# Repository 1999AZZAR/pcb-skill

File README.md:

# PCB Agent Skill

Autonomous, end-to-end PCB design, schematic capture, layout, routing, verification, and manufacturing exporter for AI coding agents (**Antigravity**, **Claude Code**, **Codex**).

Drives **KiCad 9** natively via headless command-line interfaces (`kicad-cli`), Python bindings (`pcbnew`), and direct S-expression manipulation.

---

## 1. Core Principles

1. **性价比 (Cost-Effectiveness)**: Every component is matched against real-world LCSC/JLCPCB catalog availability and pricing, netted against inventory on hand.
2. **好装配 (Hand & SMT Assemblable)**: Geometrically verified pad reachability, component orientation validation, and collision-free clearance zones.
3. **零缺陷 (Zero-Error Manufacturing Yield)**: Strict gates requiring **0 DRC errors, 0 warnings, and 0 unconnected nets** before exporting fabrication-ready packages.

---

## 2. Key Features & Architecture

* **Unified KiCad Automation Controller ([`kicad_ctl.py`](scripts/kicad/kicad_ctl.py))**:
  * 233 programmatic automation commands spanning schematics, footprints, routing, placement, netlists, and DRC checks.
  * Headless execution without requiring GUI interaction or display servers.

* **Connector Edge Orientation Engine ([`connector_rules.py`](scripts/kicad/core/connector_rules.py))**:
  * Eliminates backwards / reversed connector placement bugs.
  * Resolves KiCad library coordinate disparities where default 0° mating faces vary (USB Type-C points South $+Y$, 3.5mm Audio Jacks point West $-X$).
  * Enforces exact outward edge rotation angles across any board edge ($W=270^\circ$, $E=90^\circ$ for USB-C; $E=180^\circ$, $W=0^\circ$ for Audio Jacks).

* **Pre-Flight Placement & Clearance Validator ([`placement_validator.py`](scripts/kicad/core/placement_validator.py))**:
  * Replaces slow, iterative DRC trial-and-error with $<100\,\text{ms}$ mathematical pre-flight validation.
  * Audits true IPC courtyard polygon collisions (`F.CrtYd` / `B.CrtYd`), connector edge alignments, and $\ge 0.5\,\text{mm}$ board-edge clearances.
  * Seamlessly integrated into `scripts/kicad/drc_check.py` and `kicad_ctl.py audit-placement`.

* **Deterministic 2-Layer Router ([`autoroute_2layer.py`](scripts/kicad/autoroute_2layer.py))**:
  * Programmatic 2-layer layout builder enforcing the **5 Golden Rules**:
    1. Solid unbroken bottom ground plane (`B.Cu`).
    2. Dedicated local SMD GND via stubs straight to ground plane.
    3. Decoupled orthogonal routing (Top horizontal, Bottom short vertical jumpers).
    4. Outer margin power distribution trunks.
    5. Pin header column segregation (no diagonal crossing).
  * Built-in keepout rule area generator with explicit KiCad 9 permission flag handling.
  * Pad-level thermal relief spoke control (`ZONE_CONNECTION_FULL`) to prevent `starved_thermal` violations.

* **Hardened KiCad 9 Headless Engine**:
  * **Rule Area Permission Safety**: Prevents default blocking of tracks/vias when adding copper-pour keepouts.
  * **SWIG Iterator Guarding**: Protects against C++ pointer invalidation crashes during track deletion.
  * **Zone Island Topology Diagnostics**: Programmatic contour scanning via `zone.GetFilledPolysList()` to locate and bridge isolated ground flood islands.
  * **Rotated Pad Geometry Clearances**: Anisotropic clearance evaluations accounting for $90^\circ / 270^\circ$ orientation swaps.

* **1-Command JLCPCB Fabrication Exporter ([`export_jlcpcb.py`](scripts/kicad/export_jlcpcb.py))**:
  * RS-274X Gerbers (no X2, subtract soldermask, drill origin, 6-decimal precision).
  * Excellon drill files (separate PTH/NPTH, metric decimal).
  * JLCPCB-formatted CPL / Pick-and-Place centroid file.
  * LCSC catalog-matched Bill of Materials (BOM).
  * Photorealistic top and bottom 3D raytraced preview renders.
  * Production ZIP archive ready for 1-click ordering.
  * Independent drill census and board outline verification checkers.

---

## 3. Four-Phase Workflow Pipeline

| Phase | Output Deliverables | Gate Requirement |
| :--- | :--- | :--- |
| **1. Concept** | Functional specifications, pinout table, mechanical constraints | User confirms all physical and electrical trade-offs |
| **2. Schematic & Sourcing** | Validated `.kicad_sch`, embedded library symbols, priced BOM | `kicad-cli sch erc` passes clean; all nets asserted |
| **3. Layout & Routing** | Placed, routed, and poured `.kicad_pcb` | `kicad-cli pcb drc` **0 errors / 0 unconnected items** |
| **4. Fabrication** | Gerber archive, CPL, BOM, 3D renders in `jlcpcb_production/` | Independent verification scripts pass; package census clean |

---

## 4. Repository Structure

```
pcb-skill/
├── scripts/
│   ├── kicad/               # KiCad controller, 2-layer router, cleanup engine, JLCPCB exporter
│   ├── placement/           # Footprint courtyards, keepout checkers, clearance analysis
│   ├── routing/             # DSN/SES router runners, watchdog monitors
│   ├── verify/              # Netlist assertions, Gerber parser, drill census
│   └── run_all_tests.py     # 20-check automated regression test suite
├── skills/
│   └── pcb/
│       ├── SKILL.md         # Agent skill manifest & instruction prompt
│       └── references/      # Workflow rules, review protocols, JLC limits, bringup guides
├── docs/                    # Architecture documentation & case studies
├── setup/                   # Setup guides for KiCad, headless CLI, and browser integration
└── README.md
```

---

## 5. Automated Verification

Run the full headless test suite:

```bash
python3 scripts/run_all_tests.py
```

Validates toolchain availability, command dispatchers, board cleanup, router SES integration, DRC parsing, schematic symbol embedding, and live THT / SMT project rule checks.

---

## 6. Acknowledgments & Lineage

This skill builds upon, extends, and synthesizes concepts from two foundational open-source projects:

1. **[`daishuge/pcb-skill`](https://github.com/daishuge/pcb-skill)**:
   * Originator of the agentic hardware design workflow, real-world gating protocols, adversarial review methodology, and sourcing automation principles.
2. **[`mixelpixx/KiCAD-MCP-Server`](https://github.com/mixelpixx/KiCAD-MCP-Server)**:
   * Pioneer in programmatic KiCad automation, headless command dispatch architecture, and Model Context Protocol (MCP) tooling for computer-aided PCB design.

---

## 7. License

MIT License. See [LICENSE](LICENSE) for details.

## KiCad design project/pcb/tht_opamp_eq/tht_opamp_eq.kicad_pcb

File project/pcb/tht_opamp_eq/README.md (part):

# THT 3.3V Stereo 3-Band Equalizer & Preamp

An ultra-compact, high-fidelity, 100% Through-Hole (THT) stereo audio equalizer and headphone/line preamplifier designed for 3.3V battery or single-supply operation.

Zero surface-mount components. Optimized for hand soldering, DIY audio gear, portable headphone setups, and custom instrument tone shaping.

---

## Highlights & Specifications

| Parameter | Specification | Details |
|---|---|---|
| **Form Factor** | 88.0 mm × 61.0 mm | Ultra-compact 2-layer PCB |
| **Component Technology** | 100% Through-Hole (THT) | Easy hand assembly with basic iron |
| **Supply Voltage** | 3.3V DC (1.8V to 5.5V tolerated) | Single-cell LiFePO4, 3.7V Li-Ion (via LDO), or 2x/3x AA |
| **Active Core** | Microchip MCP6004 (DIP-14) | Quad Rail-to-Rail I/O CMOS Op-Amp |
| **Quiescent Current** | ~3.0 mA total (including LED) | Extremely power-efficient for battery use |
| **Input / Output** | Dual 3.5 mm TRS Stereo Jacks | AC-coupled audio line & headphone drive |
| **Tone Controls** | Bass, Mid, Treble (±10 to 12 dB) | Active feedback Baxandall topology |
| **Volume & Balance** | Log Volume + Linear Balance | Independent stereo level and stereo imaging |
| **Grounding** | Solid `B.Cu` Ground Plane | Full ground pour for minimum hum and noise |
| **Mounting** | 4× M3 Mounting Holes | 4.0 mm inset from board corners |
| **DRC Compliance** | **0 Errors, 0 Warnings, 0 Unconnected Nets** | 100% clean KiCad strict DRC pass |

---

## Circuit Architecture

```text
[3.5mm Stereo IN] 
       │
       ▼ (1 µF AC Coupling)
[VOL Potentiometer (50k Log)] 
       │
       ▼
[Active 3-Band Baxandall Filter] ── MCP6004 (U1A / U1D)
  ├── BASS  (100k Linear) ~100 Hz shelf (±12 dB)
  ├── MID   (100k Linear) ~1.0 kHz band (±10 dB)
  └── TREB  (100k Linear) ~10 kHz shelf (±12 dB)
       │
       ▼
[BAL Potentiometer (100k Linear)] (Stereo cross-attenuation)
       │
       ▼
[Output Driver & Buffer Stage]   ── MCP6004 (U1B / U1C)
       │
       ▼ (100 µF AC Coupling + 47Ω isolation)
[3.5mm Stereo OUT]
```

### 1. Dual Rail-to-Rail Op-Amp (MCP6004 DIP-14)
- **Sections A & D**: Left and Right inverting active tone stages. Placing the tone network in the negative feedback loop ensures low distortion and predictable boost/cut curves.
- **Sections B & C**: Left and Right output driver stages configured for clean buffering with 47Ω series output resistors (`R_STAB_L`, `R_STAB_R`) to prevent oscillation when driving capacitive cables or low-impedance headphones.

### 2. Virtual Ground Bias (VBIAS)
- Single-supply audio requires referencing AC signals to mid-rail ($V_{CC} / 2 = 1.65\text{ V}$).
- Created by a low-noise resistive divider (`R_BIAS1`, `R_BIAS2` = 100 kΩ) heavily decoupled by `C_BIAS1` (47 µF electrolytic) and `C_BIAS2` (100 nF ceramic).
- Virtual ground connects to the non-inverting pins (Pins 3 and 12 of U1) with dedicated traces and zero ground loops.

### 3. Five Control Knobs (14.0 mm Pitch)
Five dual-gang Alpha RD902F vertical potentiometers line the top edge for convenient front-panel integration:
1. **VOL** (`RV1`): 50 kΩ Dual Audio (Logarithmic) — Input gain and volume attenuation.
2. **BASS** (`RV2`): 100 kΩ Dual Linear — Low-frequency shelf response.
3. **MID** (`RV3`): 100 kΩ Dual Linear — Mid-frequency vocal and instrument presence.
4. **TREB** (`RV4`): 100 kΩ Dual Linear — High-frequency air and sparkle.
5. **BAL** (`RV5`): 100 kΩ Dual Linear — Left-to-Right stereo pan balance.

---

## Bill of Materials (BOM)

All 51 components are through-hole parts readily sourced from LCSC, Mouser, Digikey, or local electronics suppliers:

| Designator | Value | Footprint / Package | Description | Qty |
|---|---|---|---|---|
| **U1** | MCP6004-E/P | `DIP-14_W7.62mm` | Quad Rail-to-Rail I/O Op-Amp | 1 |
| **RV1** | 50k Dual Log (A50K) | `Potentiometer_Alpha_RD902F-40-00D_Dual_Vertical` | Master Stereo Volume Control | 1 |
| **RV2** | 100k Dual Lin (B100K) | `Potentiometer_Alpha_RD902F-40-00D_Dual_Vertical` | Bass Control (±12 dB @ 100 Hz) | 1 |
| **RV3** | 100k Dual Lin (B100K) | `Potentiometer_Alpha_RD902F-40-00D_Dual_Vertical` | Midrange Control (±10 dB @ 1 kHz) | 1 |
| **RV4** | 100k Dual Lin (B100K) | `Potentiometer_Alpha_RD902F-40-00D_Dual_Vertical` | Treble Control (±12 dB @ 10 kHz) | 1 |
| **RV5** | 100k Dual Lin (B100K) | `Potentiometer_Alpha_RD902F-40-00D_Dual_Vertical` | Stereo Balance Control | 1 |
| **J1** | 3.5mm Stereo | `Jack_3.5mm_Ledino_KB3SPRS_Horizontal` | Audio Input TRS Jack | 1 |
| **J2** | 3.5mm Stereo | `Jack_3.5mm_Ledino_KB3SPRS_Horizontal` | Audio Output TRS Jack | 1 |
| **J3** | 2-pin 2.54mm | `PinHeader_1x02_P2.54mm_Vertical` | DC Power Input (Pin 1: +3.3V, Pin 2: GND) | 1 |
| **D1** | 3mm Green/Red | `LED_D3.0mm` | Power Indicator LED | 1 |
| **C_PWR1** | 100 µF 16V | `CP_Radial_D5.0mm_P2.00mm` | Main Power Bulk Filter Capacitor | 1 |
| **C_PWR2** | 100 nF 50V | `C_Disc_D3.8mm_W2.6mm_P2.50mm` | High-Frequency Power Decoupling | 1 |
| **C_BIAS1** | 47 µF 16V | `CP_Radial_D5.0mm_P2.00mm` | Virtual Ground (VBIAS) Bulk Filter | 1 |
| **C_BIAS2** | 100 nF 50V | `C_Disc_D3.8mm_W2.6mm_P2.50mm` | VBIAS High-Frequency Bypass | 1 |
| **C_IN_L, C_IN_R** | 1.0 µF 50V | `C_Disc_D3.8mm_W2.6mm_P2.50mm` | Audio Input DC-Blocking Capacitors | 2 |
| **C_OUT_L, C_OUT_R** | 100 µF 16V | `CP_Radial_D5.0mm_P2.00mm` | Audio Output DC-Blocking Capacitors | 2 |
| **C_BASS_L1, C_BASS_R1** | 47 nF | `C_Disc_D3.8mm_W2.6mm_P2.50mm` | Bass Filter Frequency Setting | 2 |
| **C_MID_L1, C_MID_R1** | 22 nF | `C_Disc_D3.8mm_W2.6mm_P2.50mm` | Midrange Filter Frequency Setting | 2 |
| **C_TREB_L1, C_TREB_L2, C_TREB_R1, C_TREB_R2** | 2.2 nF | `C_Disc_D3.8mm_W2.6mm_P2.50mm` | Treble Filter Frequency Setting | 4 |
| **R_BIAS1, R_BIAS2** | 100 kΩ 1/4W | `R_Axial_DIN0207_L6.3mm_D2.5mm_P7.62mm_Horizontal` | VBIAS Voltage Divider (1% Tol) | 2 |
| **R_PWR** | 1.0 kΩ 1/4W | `R_Axial_DIN0207_L6.3mm_D2.5mm_P7.62mm_Horizontal` | LED Current Limiter | 1 |
| **R_IN_L, R_IN_R** | 100 kΩ 1/4W | `R_Axial_DIN0207_L6.3mm_D2.5mm_P7.62mm_Horizontal` | Input AC Coupling Bias Reference | 2 |
| **R_IN_EQ_L, R_IN_EQ_R** | 10 kΩ 1/4W | `R_Axial_DIN0207_L6.3mm_D2.5mm_P7.62mm_Horizontal` | Tone Stage Input Isolation | 2 |
| **R_FB_EQ_L, R_FB_EQ_R** | 10 kΩ 1/4W | `R_Axial_DIN0207_L6.3mm_D2.5mm_P7.62mm_Horizontal` | Tone Stage Feedback Loop Resistors | 2 |
| **R_BASS_L, R_BASS_R** | 10 kΩ 1/4W | `R_Axial_DIN0207_L6.3mm_D2.5mm_P7.62mm_Horizontal` | Bass Stage Shaping | 2 |
| **R_TREB_L, R_TREB_R** | 4.7 kΩ 1/4W | `R_Axial_DIN0207_L6.3mm_D2.5mm_P7.62mm_Horizontal` | Treble Stage Shaping | 2 |
| **R_FB_L, R_FB_R** | 22 kΩ 1/4W | `R_Axial_DIN0207_L6.3mm_D2.5mm_P7.62mm_Horizontal` | Driver Stage Feedback (+6 dB Gain) | 2 |
| **R_GND_L, R_GND_R** | 22 kΩ 1/4W | `R_Axial_DIN0207_L6.3mm_D2.5mm_P7.62mm_Horizontal` | Driver Stage Ground Divider | 2 |
| **R_STAB_L, R_STAB_R** | 47 Ω 1/4W | `R_Axial_DIN0207_L6.3mm_D2.5mm_P7.62mm_Horizontal` | Output Cable/Capacitive Isolation | 2 |
| **R_PULL_L, R_PULL_R** | 100 kΩ 1/4W | `R_Axial_DIN0207_L6.3mm_D2.5mm_P7.62mm_Horizontal` | Anti-Pop Jack Ground Bleeder | 2 |
| **H1, H2, H3, H4** | M3 | `MountingHole_3.2mm_M3_Pad` | 3.2 mm Plated Mounting Holes | 4 |

---

## Assembly & Soldering Sequence

To ensure easy physical access for your soldering iron tip, solder components in ascending order of height:

1. **DIP Socket (Optional)**: If using a 14-pin DIP socket for U1, solder it first.
2. **Resistors**: 1/4W axial metal-film resistors (flat against PCB).
3. **Ceramic & Film Capacitors**: 2.2 nF, 22 nF, 47 nF, 100 nF, 1 µF disc/box capacitors.
4. **Power Header & LED**: 2-pin power header `J3` and 3 mm indicator LED `D1` (note cathode flat side).
5. **Electrolytic Capacitors**: 47 µF (`C_BIAS1`), 100 µF (`C_PWR1`, `C_OUT_L`, `C_OUT_R`) — observe polarity (`+` marked on silkscreen).
6. **Audio Jacks**: 3.5 mm TRS connectors `J1` and `J2`.
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
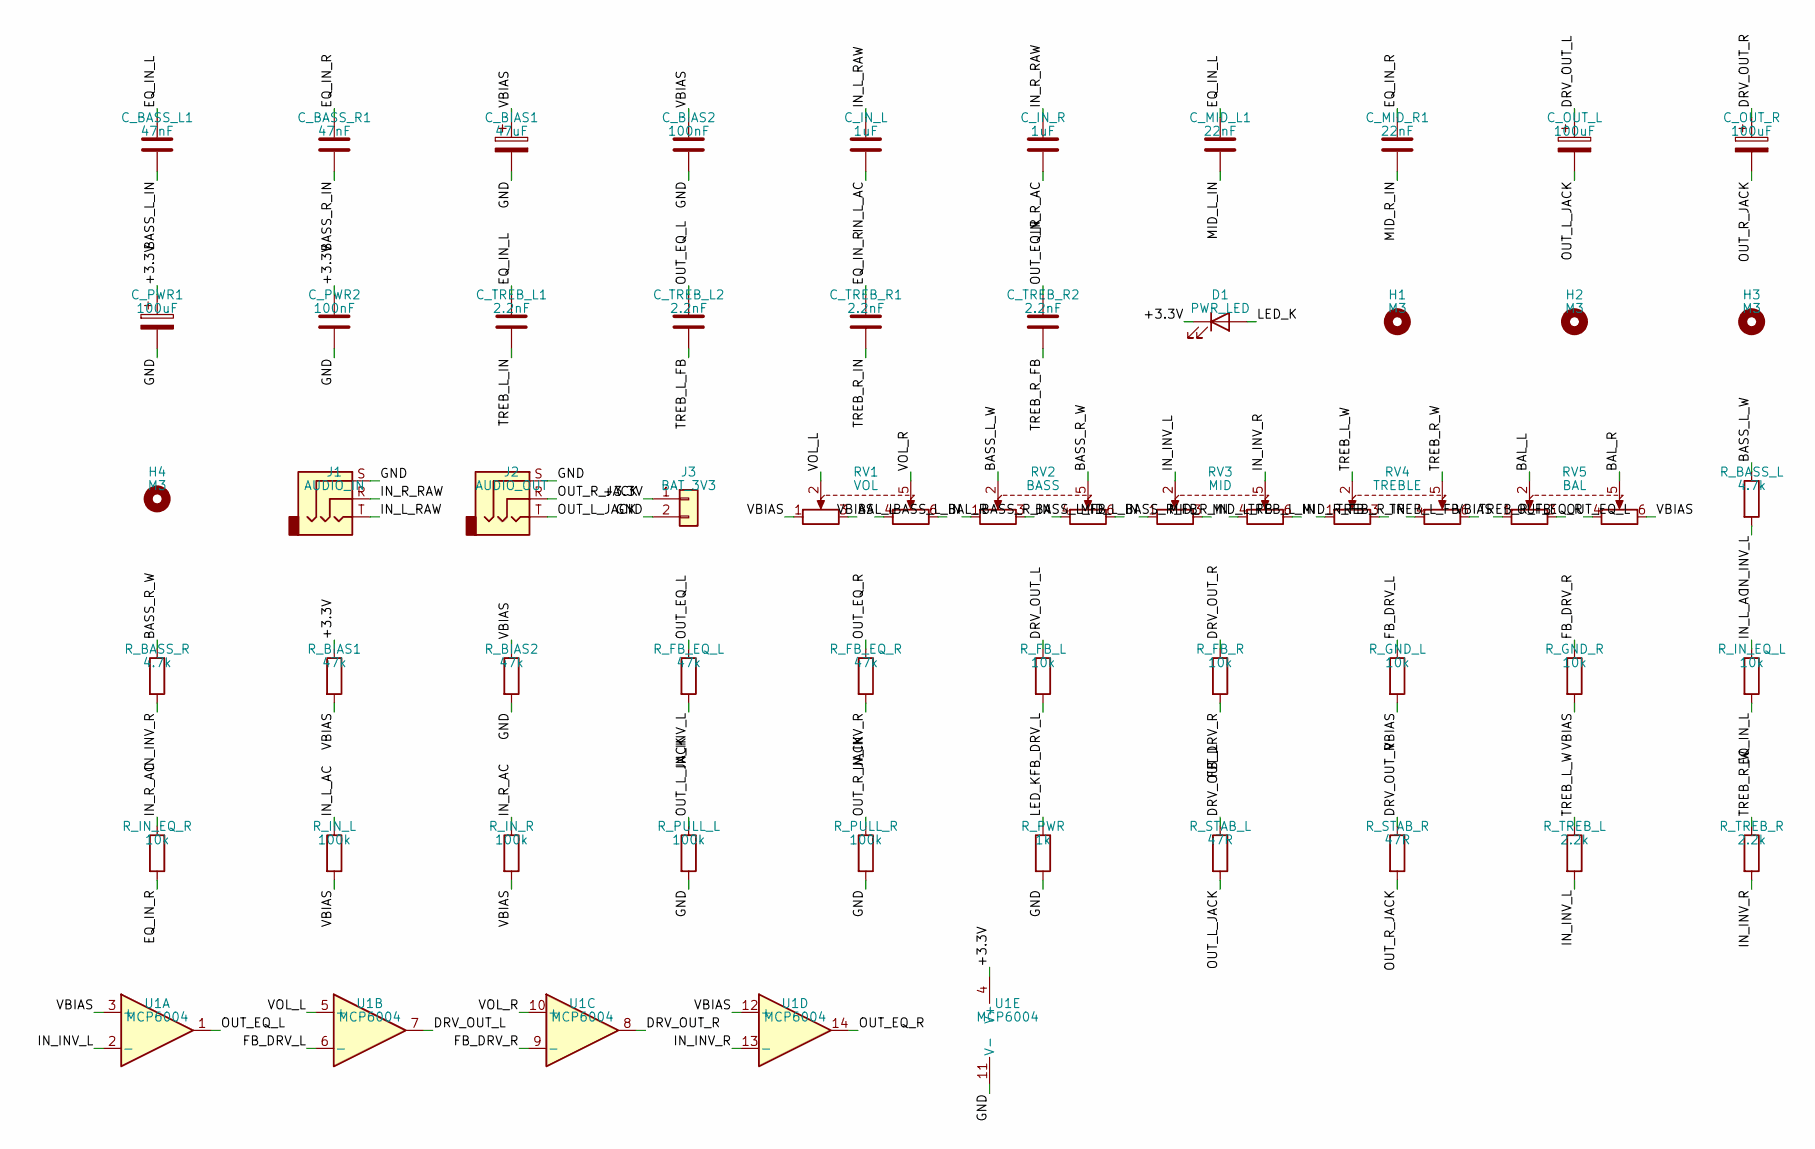
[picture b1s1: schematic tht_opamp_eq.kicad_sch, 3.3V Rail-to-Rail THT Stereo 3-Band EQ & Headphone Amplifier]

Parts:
C_BASS_L1: 47nF; C_Disc_D3.8mm_W2.6mm_P2.50mm
C_BASS_R1: 47nF; C_Disc_D3.8mm_W2.6mm_P2.50mm
C_BIAS1: 47uF; CP_Radial_D5.0mm_P2.00mm
C_BIAS2: 100nF; C_Disc_D3.8mm_W2.6mm_P2.50mm
C_IN_L: 1uF; C_Disc_D3.8mm_W2.6mm_P2.50mm
C_IN_R: 1uF; C_Disc_D3.8mm_W2.6mm_P2.50mm
C_MID_L1: 22nF; C_Disc_D3.8mm_W2.6mm_P2.50mm
C_MID_R1: 22nF; C_Disc_D3.8mm_W2.6mm_P2.50mm
C_OUT_L: 100uF; CP_Radial_D5.0mm_P2.00mm
C_OUT_R: 100uF; CP_Radial_D5.0mm_P2.00mm
C_PWR1: 100uF; CP_Radial_D5.0mm_P2.00mm
C_PWR2: 100nF; C_Disc_D3.8mm_W2.6mm_P2.50mm
C_TREB_L1, C_TREB_L2: 2.2nF; C_Disc_D3.8mm_W2.6mm_P2.50mm
C_TREB_R1, C_TREB_R2: 2.2nF; C_Disc_D3.8mm_W2.6mm_P2.50mm
D1: PWR_LED; LED_D3.0mm
H1, H2, H3, H4: M3; MountingHole_3.2mm_M3
J1: AUDIO_IN; Jack_3.5mm_Ledino_KB3SPRS_Horizontal
J2: AUDIO_OUT; Jack_3.5mm_Ledino_KB3SPRS_Horizontal
J3: BAT_3V3; PinHeader_1x02_P2.54mm_Vertical
RV1: VOL; Potentiometer_Alpha_RD902F-40-00D_Dual_Vertical_CircularHol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
RV2: BASS; Potentiometer_Alpha_RD902F-40-00D_Dual_Vertical_CircularHol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
RV3: MID; Potentiometer_Alpha_RD902F-40-00D_Dual_Vertical_CircularHol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
RV4: TREBLE; Potentiometer_Alpha_RD902F-40-00D_Dual_Vertical_CircularHol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
RV5: BAL; Potentiometer_Alpha_RD902F-40-00D_Dual_Vertical_CircularHol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
R_BASS_L: 4.7k; R_Axial_DIN0204_L3.6mm_D1.6mm_P5.08mm_Horizontal
R_BASS_R: 4.7k; R_Axial_DIN0204_L3.6mm_D1.6mm_P5.08mm_Horizontal
R_BIAS1, R_BIAS2: 47k; R_Axial_DIN0204_L3.6mm_D1.6mm_P5.08mm_Horizontal
R_FB_EQ_L: 47k; R_Axial_DIN0204_L3.6mm_D1.6mm_P5.08mm_Horizontal
R_FB_EQ_R: 47k; R_Axial_DIN0204_L3.6mm_D1.6mm_P5.08mm_Horizontal
R_FB_L: 10k; R_Axial_DIN0204_L3.6mm_D1.6mm_P5.08mm_Horizontal
R_FB_R: 10k; R_Axial_DIN0204_L3.6mm_D1.6mm_P5.08mm_Horizontal
R_GND_L: 10k; R_Axial_DIN0204_L3.6mm_D1.6mm_P5.08mm_Horizontal
R_GND_R: 10k; R_Axial_DIN0204_L3.6mm_D1.6mm_P5.08mm_Horizontal
R_IN_EQ_L: 10k; R_Axial_DIN0204_L3.6mm_D1.6mm_P5.08mm_Horizontal
R_IN_EQ_R: 10k; R_Axial_DIN0204_L3.6mm_D1.6mm_P5.08mm_Horizontal
R_IN_L: 100k; R_Axial_DIN0204_L3.6mm_D1.6mm_P5.08mm_Horizontal
R_IN_R: 100k; R_Axial_DIN0204_L3.6mm_D1.6mm_P5.08mm_Horizontal
R_PULL_L: 100k; R_Axial_DIN0204_L3.6mm_D1.6mm_P5.08mm_Horizontal
R_PULL_R: 100k; R_Axial_DIN0204_L3.6mm_D1.6mm_P5.08mm_Horizontal
R_PWR: 1k; R_Axial_DIN0204_L3.6mm_D1.6mm_P5.08mm_Horizontal
R_STAB_L: 47R; R_Axial_DIN0204_L3.6mm_D1.6mm_P5.08mm_Horizontal
R_STAB_R: 47R; R_Axial_DIN0204_L3.6mm_D1.6mm_P5.08mm_Horizontal
R_TREB_L: 2.2k; R_Axial_DIN0204_L3.6mm_D1.6mm_P5.08mm_Horizontal
R_TREB_R: 2.2k; R_Axial_DIN0204_L3.6mm_D1.6mm_P5.08mm_Horizontal
U1: MCP6004; DIP-14_W7.62mm

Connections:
+3.3V: C_PWR1.1, C_PWR2.1, D1.1 (K), J3.1, R_BIAS1.1, U1.4 (V+)
BAL_L: RV1.3, RV5.2
BAL_R: RV1.6, RV5.5
BASS_L_FB: RV2.3
BASS_L_IN: C_BASS_L1.2, RV2.1
BASS_L_W: RV2.2, R_BASS_L.1
BASS_R_FB: RV2.6
BASS_R_IN: C_BASS_R1.2, RV2.4
BASS_R_W: RV2.5, R_BASS_R.1
DRV_OUT_L: C_OUT_L.1, R_FB_L.1, R_STAB_L.1, U1.7
DRV_OUT_R: C_OUT_R.1, R_FB_R.1, R_STAB_R.1, U1.8
EQ_IN_L: C_BASS_L1.1, C_MID_L1.1, C_TREB_L1.1, R_IN_EQ_L.2
EQ_IN_R: C_BASS_R1.1, C_MID_R1.1, C_TREB_R1.1, R_IN_EQ_R.2
FB_DRV_L: R_FB_L.2, R_GND_L.1, U1.6 (-)
FB_DRV_R: R_FB_R.2, R_GND_R.1, U1.9 (-)
GND: C_BIAS1.2, C_BIAS2.2, C_PWR1.2, C_PWR2.2, J1.RN, J1.S, J1.TN, J2.RN, J2.S, J2.TN, J3.2, R_BIAS2.2, R_PULL_L.2, R_PULL_R.2, R_PWR.2, U1.11 (V-)
IN_INV_L: RV3.2, R_BASS_L.2, R_FB_EQ_L.2, R_TREB_L.2, U1.2 (-)
IN_INV_R: RV3.5, R_BASS_R.2, R_FB_EQ_R.2, R_TREB_R.2, U1.13 (-)
IN_L_AC: C_IN_L.2, R_IN_EQ_L.1, R_IN_L.1
IN_L_RAW: C_IN_L.1, J1.T
IN_R_AC: C_IN_R.2, R_IN_EQ_R.1, R_IN_R.1
IN_R_RAW: C_IN_R.1, J1.R
LED_K: D1.2 (A), R_PWR.1
MID_L_FB: RV3.3
MID_L_IN: C_MID_L1.2, RV3.1
MID_R_FB: RV3.6
MID_R_IN: C_MID_R1.2, RV3.4
OUT_EQ_L: C_TREB_L2.1, RV5.3, R_FB_EQ_L.1, U1.1
OUT_EQ_R: C_TREB_R2.1, RV5.4, R_FB_EQ_R.1, U1.14
OUT_L_JACK: C_OUT_L.2, J2.T, R_PULL_L.1, R_STAB_L.2
OUT_R_JACK: C_OUT_R.2, J2.R, R_PULL_R.1, R_STAB_R.2
TREB_L_FB: C_TREB_L2.2, RV4.3
TREB_L_IN: C_TREB_L1.2, RV4.1
TREB_L_W: RV4.2, R_TREB_L.1
TREB_R_FB: C_TREB_R2.2, RV4.6
TREB_R_IN: C_TREB_R1.2, RV4.4
TREB_R_W: RV4.5, R_TREB_R.1
VBIAS: C_BIAS1.1, C_BIAS2.1, RV1.1, RV1.4, RV5.1, RV5.6, R_BIAS1.2, R_BIAS2.1, R_GND_L.2, R_GND_R.2, R_IN_L.2, R_IN_R.2, U1.3 (+), U1.12 (+)
VOL_L: RV1.2, U1.5 (+)
VOL_R: RV1.5, U1.10 (+)

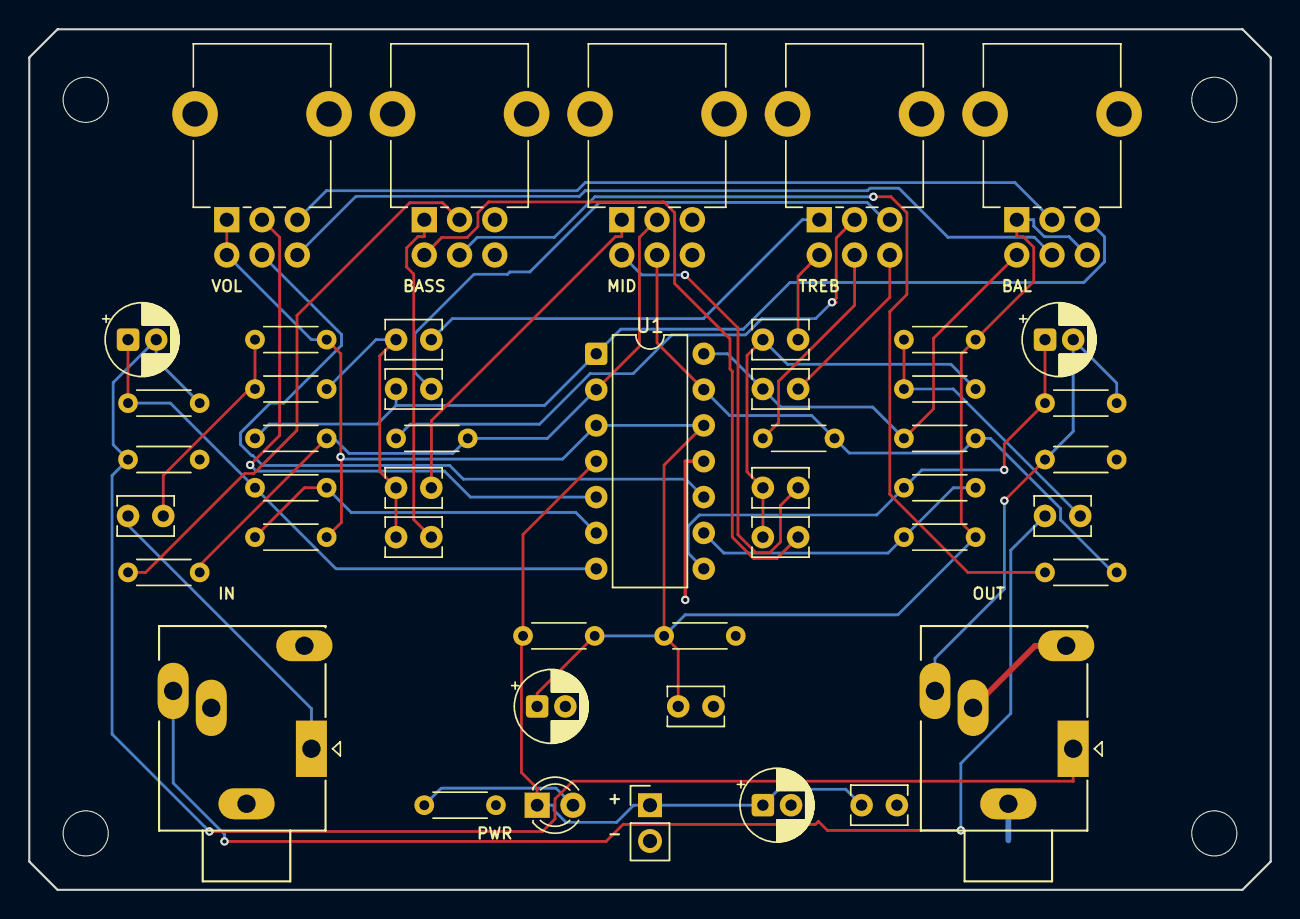
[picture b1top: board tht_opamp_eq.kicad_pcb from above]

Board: 2 copper layers, 88.0 x 61.0 mm, 51 parts (0 on the bottom side), 36 nets.

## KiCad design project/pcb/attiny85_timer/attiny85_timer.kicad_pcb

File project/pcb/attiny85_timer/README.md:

# ATtiny85 & NE555 Timer Experimental Development Board

An autonomous hybrid timing & processing module combining an **Atmel ATtiny85-20SU** microcontroller with a hardware **TI NE555D** precision timer. Designed and validated using **KiCad 9** with production-ready JLCPCB fabrication deliverables.

---

## 📌 Architecture Overview

- **Microcontroller**: ATtiny85-20SU (8-pin SOIC, 8 MHz internal oscillator or external clocking).
- **Hardware Timer**: NE555D (8-pin SOIC configured in astable multivibrator mode).
- **Power Delivery**: 5V via standard USB-C receptacle (`TYPE-C-31-M-12`) with dual 5.1k CC pull-down resistors for USB-PD source compliance.
- **In-System Programming**: Standard 2x3 2.54mm AVR-ISP programming header for flashing firmware with USBasp / ArduinoISP.
- **Auxiliary Output**: 1x4 2.54mm pin header exposing power, timer pulse output, and microcontroller PWM/GPIO.
- **Visual Telemetry**:
  - `D1` (Green): 5V Main Power Rail
  - `D2` (Yellow): NE555 Hardware Pulse Output Indicator
  - `D3` (Blue): ATtiny85 GPIO Status LED

---

## 🗂️ Project File Structure

```text
pcb_trial/
├── README.md                      # Complete project documentation & hardware spec
├── attiny85_timer.kicad_pro       # KiCad 9 Project metadata
├── attiny85_timer.kicad_sch       # KiCad 9 Schematic with fully embedded lib_symbols
├── attiny85_timer.kicad_pcb       # KiCad 9 2-Layer Board Layout & Ground Planes
└── jlcpcb_production/             # One-click manufacturing package
    ├── attiny85_timer_gerber_jlcpcb.zip  # Gerber (RS-274X) + Excellon drill package
    ├── attiny85_timer_bom_jlcpcb.csv     # Bill of Materials formatted for JLCPCB SMT
    ├── attiny85_timer_cpl_jlcpcb.csv     # Component Placement List (Centroid / Pick-and-Place)
    ├── attiny85_timer_render_top.png     # Photorealistic 3D top render
    └── attiny85_timer_render_bottom.png  # Photorealistic 3D bottom render
```

---

## ⚡ Bill of Materials (BOM)

| Designator | Description | Footprint | LCSC Part # |
| :--- | :--- | :--- | :--- |
| **U1** | NE555D Precision Timer | SOIC-8_3.9x4.9mm_P1.27mm | C46749 |
| **U2** | ATtiny85-20SU AVR MCU | SOIC-8_3.9x4.9mm_P1.27mm | C44533 |
| **J1** | USB-C 16-Pin Receptacle | HRO TYPE-C-31-M-12 | C165948 |
| **J2** | AVR-ISP 2x3 Pin Header | PinHeader_2x03_P2.54mm_Vertical | C225434 |
| **J3** | AUX 1x4 Pin Header | PinHeader_1x04_P2.54mm_Vertical | C2243 |
| **C1** | 10µF 16V Ceramic Cap | C_0805_2012Metric | C15850 |
| **C2** | 1µF 16V Ceramic Cap | C_0805_2012Metric | C28323 |
| **C3** | 10nF 50V Ceramic Cap | C_0805_2012Metric | C1710 |
| **C4, C5** | 100nF 50V Decoupling Caps | C_0805_2012Metric | C49678 |
| **D1** | Green LED (Power) | LED_0805_2012Metric | C2297 |
| **D2** | Yellow LED (Timer Pulse) | LED_0805_2012Metric | C2296 |
| **D3** | Blue LED (MCU Status) | LED_0805_2012Metric | C2293 |
| **R1, R2** | 5.1kΩ 1% (USB-C CC) | R_0805_2012Metric | C17637 |
| **R3, R4, R8**| 1kΩ 1% (LED Ballast) | R_0805_2012Metric | C17513 |
| **R5, R7** | 10kΩ 1% Pull-up | R_0805_2012Metric | C17414 |
| **R6** | 47kΩ 1% Timing Resistor | R_0805_2012Metric | C17713 |

---

## 🛠️ Verification & DRC Status

- **Design Rule Checks (DRC)**:
  - Errors: `0`
  - Warnings: `0`
  - Unconnected Nets: `0`
- **KiCad Compatibility**: Built and natively formatted for **KiCad v9.0+** (`(version 20250114)` schematic, `(version 20241229)` PCB) with 100% self-contained graphics.

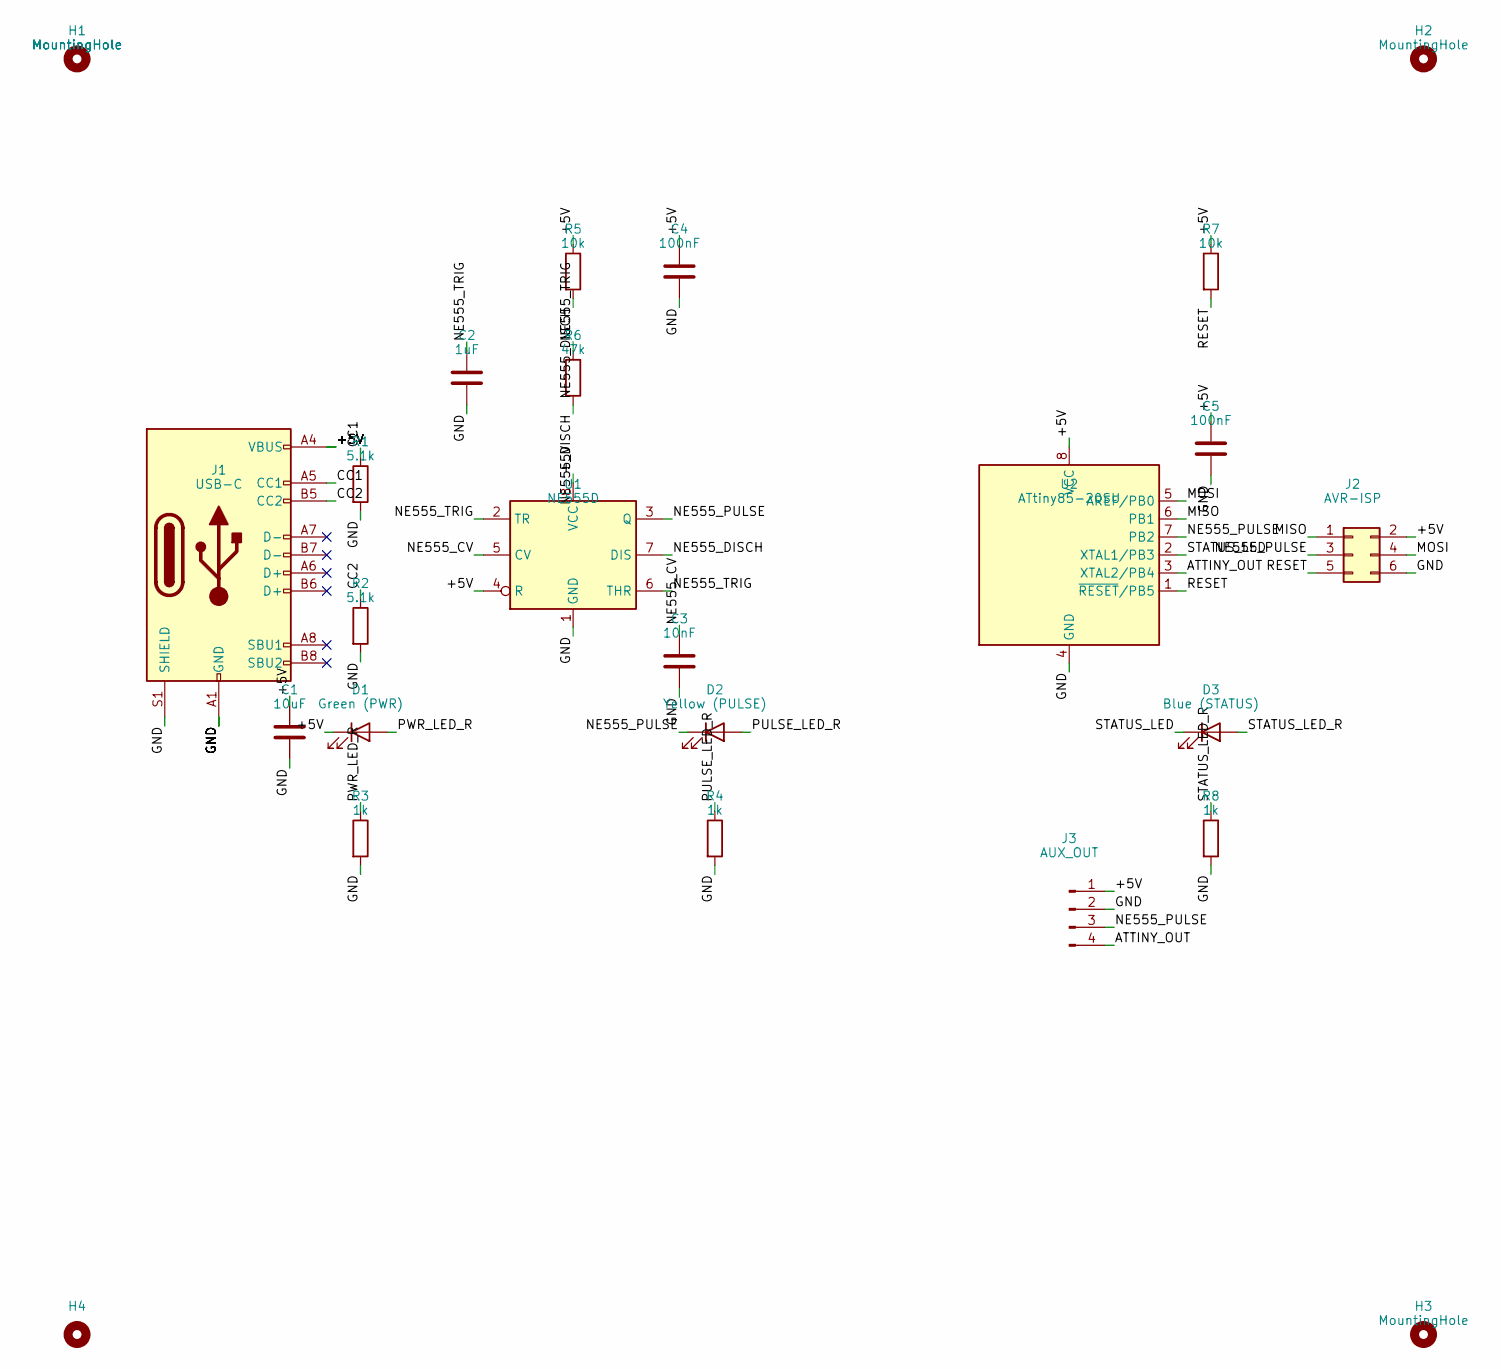
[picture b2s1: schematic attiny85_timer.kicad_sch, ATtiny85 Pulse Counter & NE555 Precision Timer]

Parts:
C1: 10uF; C_0805_2012Metric
C2: 1uF; C_0805_2012Metric
C3: 10nF; C_0805_2012Metric
C4, C5: 100nF; C_0805_2012Metric
D1: Green (PWR); LED_0805_2012Metric
D2: Yellow (PULSE); LED_0805_2012Metric
D3: Blue (STATUS); LED_0805_2012Metric
H1, H2, H3, H4: MountingHole; MountingHole_3.2mm_M3
J1: USB-C; USB_C_Receptacle_HRO_TYPE-C-31-M-12
J2: AVR-ISP; PinHeader_2x03_P2.54mm_Vertical
J3: AUX_OUT; PinHeader_1x04_P2.54mm_Vertical
R1, R2: 5.1k; R_0805_2012Metric
R3, R4, R8: 1k; R_0805_2012Metric
R5, R7: 10k; R_0805_2012Metric
R6: 47k; R_0805_2012Metric
U1: NE555D; SOIC-8_3.9x4.9mm_P1.27mm
U2: ATtiny85-20SU; SOIC-8_3.9x4.9mm_P1.27mm

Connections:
+5V: C1.1, C4.1, C5.1, D1.1 (K), J1.A4 (VBUS), J1.A9 (VBUS), J1.B4 (VBUS), J1.B9 (VBUS), J2.2, J3.1, R5.1, R7.1, U1.4 (R), U1.8 (VCC), U2.8 (VCC)
ATTINY_OUT: J3.4, U2.3 (XTAL2/PB4)
CC1: J1.A5 (CC1), R1.1
CC2: J1.B5 (CC2), R2.1
GND: C1.2, C2.2, C3.2, C4.2, C5.2, J1.A1 (GND), J1.A12 (GND), J1.B1 (GND), J1.B12 (GND), J1.S1 (SHIELD), J2.6, J3.2, R1.2, R2.2, R3.2, R4.2, R8.2, U1.1 (GND), U2.4 (GND)
MISO: J2.1, U2.6 (PB1)
MOSI: J2.4, U2.5 (AREF/PB0)
NE555_CV: C3.1, U1.5 (CV)
NE555_DISCH: R5.2, R6.2, U1.7 (DIS)
NE555_PULSE: D2.1 (K), J2.3, J3.3, U1.3 (Q), U2.7 (PB2)
NE555_TRIG: C2.1, R6.1, U1.2 (TR), U1.6 (THR)
PULSE_LED_R: D2.2 (A), R4.1
PWR_LED_R: D1.2 (A), R3.1
RESET: J2.5, R7.2, U2.1 (~RESET/PB5)
STATUS_LED: D3.1 (K), U2.2 (XTAL1/PB3)
STATUS_LED_R: D3.2 (A), R8.1

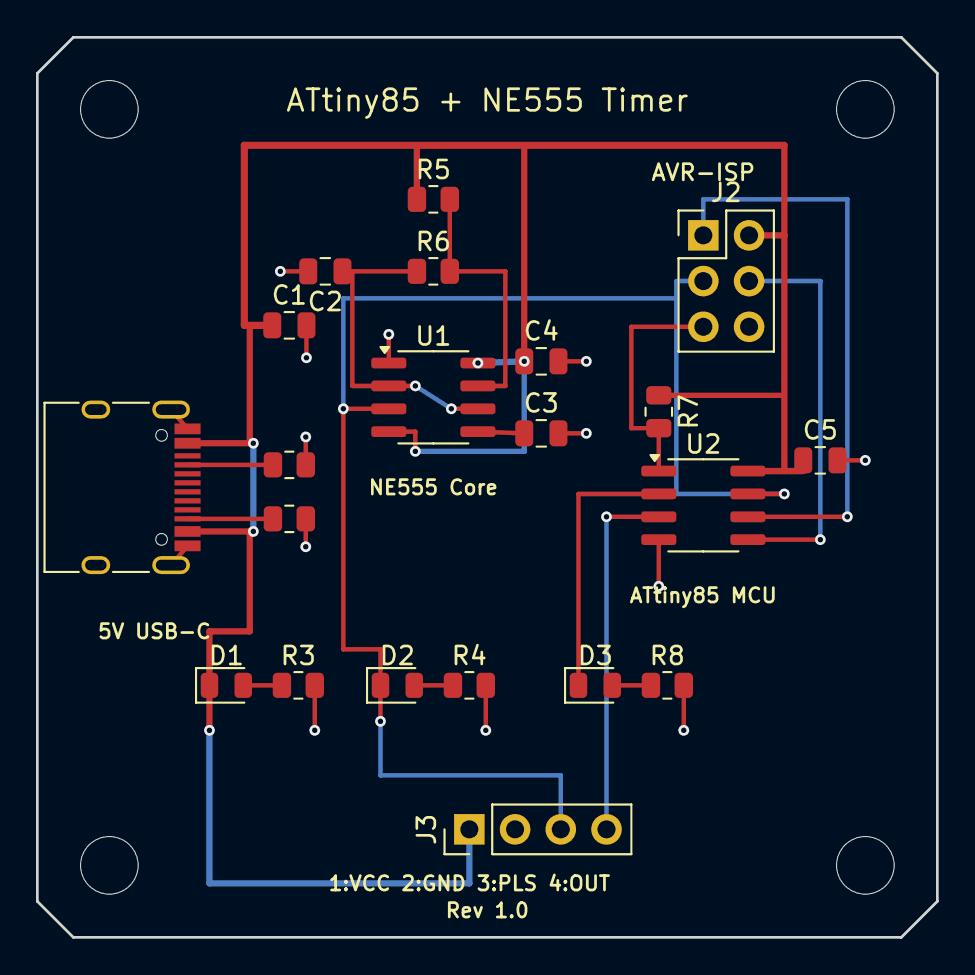
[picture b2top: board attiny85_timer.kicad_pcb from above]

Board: 2 copper layers, 50.0 x 50.0 mm, 25 parts (0 on the bottom side), 16 nets.

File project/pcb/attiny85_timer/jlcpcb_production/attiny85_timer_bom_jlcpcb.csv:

"Refs","Value","Footprint","Qty","DNP"
"C1","10uF","Capacitor_SMD:C_0805_2012Metric","1",""
"C2","1uF","Capacitor_SMD:C_0805_2012Metric","1",""
"C3","10nF","Capacitor_SMD:C_0805_2012Metric","1",""
"C4","100nF","Capacitor_SMD:C_0805_2012Metric","1",""
"C5","100nF","Capacitor_SMD:C_0805_2012Metric","1",""
"D1","Green (PWR)","LED_SMD:LED_0805_2012Metric","1",""
"D2","Yellow (PULSE)","LED_SMD:LED_0805_2012Metric","1",""
"D3","Blue (STATUS)","LED_SMD:LED_0805_2012Metric","1",""
"J1","USB-C","Connector_USB:USB_C_Receptacle_HRO_TYPE-C-31-M-12","1",""
"J2","AVR-ISP","Connector_PinHeader_2.54mm:PinHeader_2x03_P2.54mm_Vertical","1",""
"J3","AUX_OUT","Connector_PinHeader_2.54mm:PinHeader_1x04_P2.54mm_Vertical","1",""
"R1","5.1k","Resistor_SMD:R_0805_2012Metric","1",""
"R2","5.1k","Resistor_SMD:R_0805_2012Metric","1",""
"R3","1k","Resistor_SMD:R_0805_2012Metric","1",""
"R4","1k","Resistor_SMD:R_0805_2012Metric","1",""
"R5","10k","Resistor_SMD:R_0805_2012Metric","1",""
"R6","47k","Resistor_SMD:R_0805_2012Metric","1",""
"R7","10k","Resistor_SMD:R_0805_2012Metric","1",""
"R8","1k","Resistor_SMD:R_0805_2012Metric","1",""
"U1","NE555D","Package_SO:SOIC-8_3.9x4.9mm_P1.27mm","1",""
"U2","ATtiny85-20SU","Package_SO:SOIC-8_3.9x4.9mm_P1.27mm","1",""

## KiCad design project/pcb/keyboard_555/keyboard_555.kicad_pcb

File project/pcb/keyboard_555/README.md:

# 555 Mini Keyboard / Synthesizer Organ

A compact 7-note musical keyboard and synthesizer organ built around a single classic NE555 timer in an astable multivibrator configuration. Designed from schematic to 2-layer PCB fabrication in KiCad 9 with 100% production DRC/ERC pass (`--severity-all`: 0 violations, 0 warnings, 0 unconnected items).

---

## 1. Features & Specifications

- **Sound Generation**: Single NE555 precision bipolar timer (DIP-8 socketed) running in an astable multivibrator topology.
- **7-Note Diatonic Scale**: C5 to B5 notes triggered by 6x6mm tactile switches.
- **Silent Idle Operation**: Pressing any key inserts that note's tuning resistor between Discharge (Pin 7) and Threshold/Trigger (Pins 2/6), immediately sounding the tone. Releasing silence the output.
- **Dual Audio Output**:
  - Onboard 12mm magnetic buzzer/transducer for stand-alone acoustic playback.
  - 3.5mm stereo headphone jack (PJ320D) for line-out / private listening.
  - 10k horizontal trimmer potentiometer (`RV1`) for master volume control.
- **Power Architecture**:
  - Reversible USB Type-C connector with dual 5.1k CC pull-downs for 5V negotiation from any standard USB-C charger or PC port.
  - SPDT slide switch for hard power cutoff.
  - 3mm red LED power indicator.
  - 100µF electrolytic decoupling capacitor for clean oscillator supply rails.
- **Board Dimensions**: 100.0 mm × 48.0 mm (standard JLCPCB economic panel size), 2-layer 1.6mm FR4, 1oz copper, 3mm corner chamfers, and 4× M3 mounting holes.

---

## 2. Musical Note Tuning & Calculations

The NE555 oscillates in astable mode with timing capacitor $C_1 = 100\,\text{nF}$ and fixed pull-up resistor $R_A = 1.0\,\text{k}\Omega$. When key $i$ is pressed, tuning resistor $R_i$ is engaged in the timing loop:

$$f = \frac{1.44}{(R_A + 2 R_i) \cdot C_1}$$

$$R_i = \frac{1}{2} \left( \frac{1.44}{f \cdot C_1} - R_A \right)$$

| Note | Target Freq (Hz) | Calculated $R_i$ ($\text{k}\Omega$) | Standard Value ($\text{k}\Omega$) | Actual Freq (Hz) | Error |
| :--- | :--- | :--- | :--- | :--- | :--- |
| **C5** | 523.25 | 13.26 | **13k** | 533.3 | +1.9% |
| **D5** | 587.33 | 11.26 | **12k** | 576.0 | -1.9% |
| **E5** | 659.25 | 9.92 | **10k** | 685.7 | +4.0% |
| **F5** | 698.46 | 9.31 | **9.1k** | 750.0 | +7.3% |
| **G5** | 783.99 | 8.18 | **8.2k** | 827.6 | +5.5% |
| **A5** | 880.00 | 7.18 | **7.5k** | 900.0 | +2.2% |
| **B5** | 987.77 | 6.29 | **6.8k** | 986.3 | -0.1% |

---

## 3. Bill of Materials (BOM)

| Ref | Qty | Value | Description | Package / Footprint |
| :--- | :--- | :--- | :--- | :--- |
| **U1** | 1 | NE555P | Precision Timer IC | DIP-8 (W7.62mm socket) |
| **J1** | 1 | USB_C_16P | USB Type-C Receptacle | HRO TYPE-C-31-M-12 |
| **J2** | 1 | Audio_Jack | 3.5mm Stereo Headphone Jack | PJ320D Horizontal |
| **BZ1** | 1 | Buzzer | 12mm Magnetic Transducer | 7.6mm Pin Pitch (RM7.6) |
| **SW_PWR** | 1 | SPDT | Slide Switch Straight | OS102011MS2Q |
| **SW1–SW7** | 7 | SW_Key | 6x6mm Tactile Push Switch | 6.5mm × 4.5mm Pitch |
| **RV1** | 1 | 10k | Trimmer Potentiometer | Bourns 3386P Vertical |
| **D_PWR** | 1 | RED | 3mm Red LED | LED_D3.0mm THT |
| **C_PWR** | 1 | 100µF | Electrolytic Filter Cap (16V+) | Radial D6.3mm P2.5mm |
| **C_OUT** | 1 | 10µF | AC Coupling Output Cap | Radial D6.3mm P2.5mm |
| **C1** | 1 | 100nF | Ceramic Timing Capacitor | Disc D5.0mm P2.5mm |
| **C2** | 1 | 10nF | CV Bypass Capacitor | Disc D5.0mm P2.5mm |
| **R_A** | 1 | 1k | Fixed Timing Pull-up Resistor | Axial DIN0207 1/4W |
| **R_PWR** | 1 | 1k | LED Current Limiting Resistor | Axial DIN0207 1/4W |
| **R_CC1, R_CC2** | 2 | 5.1k | USB-C CC Configuration Resistors | SMD 0805 (2012 Metric) |
| **R1** | 1 | 13k | C5 Tuning Resistor | Axial DIN0207 1/4W |
| **R2** | 1 | 12k | D5 Tuning Resistor | Axial DIN0207 1/4W |
| **R3** | 1 | 10k | E5 Tuning Resistor | Axial DIN0207 1/4W |
| **R4** | 1 | 9.1k | F5 Tuning Resistor | Axial DIN0207 1/4W |
| **R5** | 1 | 8.2k | G5 Tuning Resistor | Axial DIN0207 1/4W |
| **R6** | 1 | 7.5k | A5 Tuning Resistor | Axial DIN0207 1/4W |
| **R7** | 1 | 6.8k | B5 Tuning Resistor | Axial DIN0207 1/4W |

---

## 4. Verification & DRC/ERC Results

| Verification Check | Standard | Result | Status |
| :--- | :--- | :--- | :--- |
| **KiCad Board DRC** | `--severity-all` | **0 violations, 0 unconnected items** | ✔️ PASS |
| **KiCad Schematic ERC** | `--severity-all` | **0 violations, 0 warnings** | ✔️ PASS |
| **Drill Census** | Excellon verification | **95 holes in 2 files (PTH & NPTH)** | ✔️ PASS |
| **Board Outline** | Edge_Cuts inspection | **Closed continuous contour (Edge_Cuts.gm1)** | ✔️ PASS |
| **Netlist Integrity** | Schematic vs PCB | **100% net match across all 19 nets** | ✔️ PASS |

---

## 5. Manufacturing Package (`jlcpcb_production/`)

Ready for instant one-click ordering on [JLCPCB](https://jlcpcb.com/):
- **`keyboard_555_gerber_jlcpcb.zip`**: Complete RS-274X Gerbers and Excellon drill files.
- **`keyboard_555_bom_jlcpcb.csv`**: Formatted BOM with component values and footprints.
- **`keyboard_555_cpl_jlcpcb.csv`**: Centroid / pick-and-place coordinate file for SMD components.
- **`keyboard_555_render_top.png`**: High-resolution 3D raytraced top render.
- **`keyboard_555_render_bottom.png`**: High-resolution 3D raytraced bottom render.

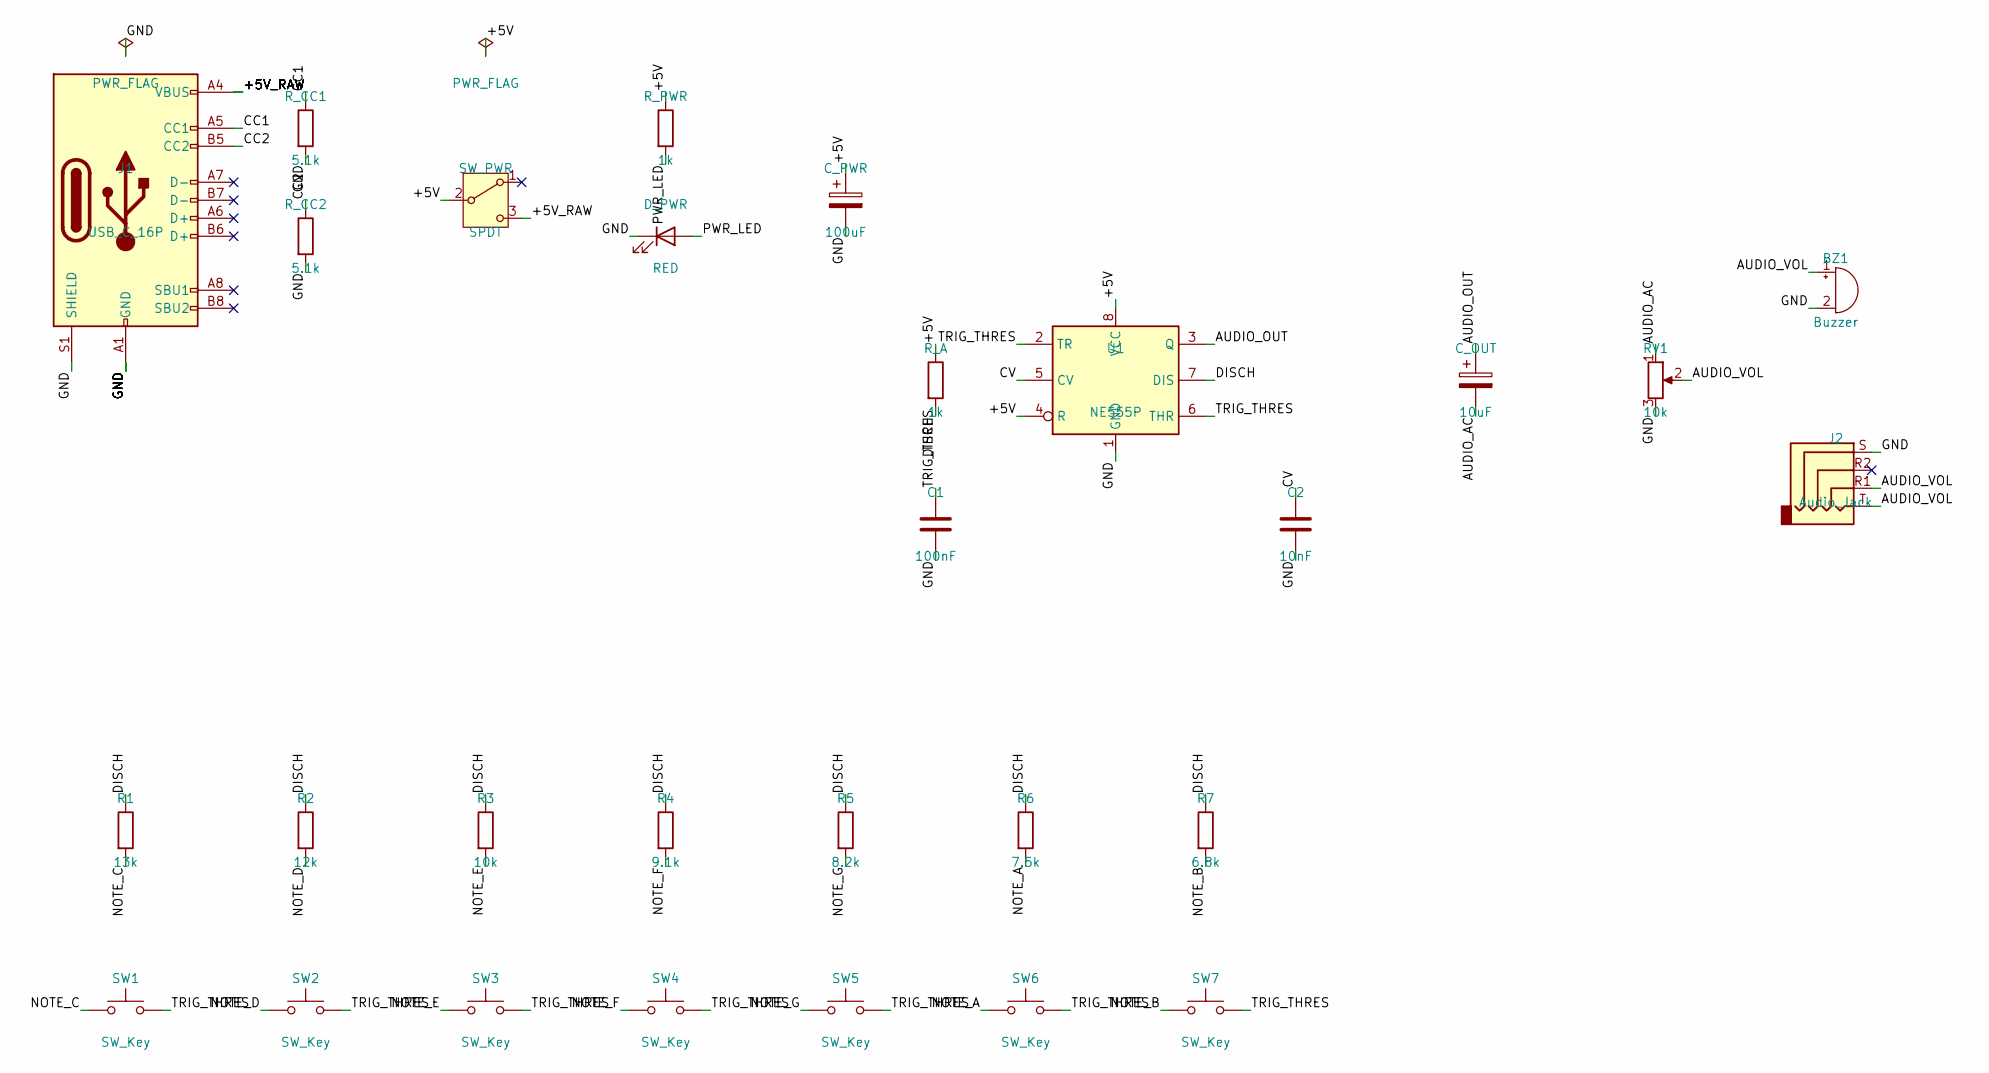
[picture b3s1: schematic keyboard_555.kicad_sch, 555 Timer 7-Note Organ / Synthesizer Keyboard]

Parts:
BZ1: Buzzer; Buzzer_12x9.5RM7.6
C1: 100nF; C_Disc_D5.0mm_W2.5mm_P2.50mm
C2: 10nF; C_Disc_D5.0mm_W2.5mm_P2.50mm
C_OUT: 10uF; CP_Radial_D6.3mm_P2.50mm
C_PWR: 100uF; CP_Radial_D6.3mm_P2.50mm
D_PWR: RED; LED_D3.0mm
J1: USB_C_16P; USB_C_Receptacle_HRO_TYPE-C-31-M-12
J2: Audio_Jack; Jack_3.5mm_PJ320D_Horizontal
R1: 13k; R_Axial_DIN0207_L6.3mm_D2.5mm_P7.62mm_Horizontal
R2: 12k; R_Axial_DIN0207_L6.3mm_D2.5mm_P7.62mm_Horizontal
R3: 10k; R_Axial_DIN0207_L6.3mm_D2.5mm_P7.62mm_Horizontal
R4: 9.1k; R_Axial_DIN0207_L6.3mm_D2.5mm_P7.62mm_Horizontal
R5: 8.2k; R_Axial_DIN0207_L6.3mm_D2.5mm_P7.62mm_Horizontal
R6: 7.5k; R_Axial_DIN0207_L6.3mm_D2.5mm_P7.62mm_Horizontal
R7: 6.8k; R_Axial_DIN0207_L6.3mm_D2.5mm_P7.62mm_Horizontal
RV1: 10k; Potentiometer_Bourns_3386P_Vertical
R_A: 1k; R_Axial_DIN0207_L6.3mm_D2.5mm_P7.62mm_Horizontal
R_CC1, R_CC2: 5.1k; R_0805_2012Metric
R_PWR: 1k; R_Axial_DIN0207_L6.3mm_D2.5mm_P7.62mm_Horizontal
SW1, SW2, SW3, SW4, SW5, SW6, SW7: SW_Key; SW_PUSH_6mm_H5mm
SW_PWR: SPDT; SW_Slide_SPDT_Straight_CK_OS102011MS2Q
U1: NE555P; DIP-8_W7.62mm_Socket

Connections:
+5V: C_PWR.1, R_A.1, R_PWR.1, SW_PWR.2 (B), U1.4 (R), U1.8 (VCC)
+5V_RAW: J1.A4 (VBUS), J1.A9 (VBUS), J1.B4 (VBUS), J1.B9 (VBUS), SW_PWR.3 (C)
AUDIO_AC: C_OUT.2, RV1.1
AUDIO_OUT: C_OUT.1, U1.3 (Q)
AUDIO_VOL: BZ1.1 (+), J2.R1, J2.T, RV1.2
CC1: J1.A5 (CC1), R_CC1.1
CC2: J1.B5 (CC2), R_CC2.1
CV: C2.1, U1.5 (CV)
DISCH: R1.1, R2.1, R3.1, R4.1, R5.1, R6.1, R7.1, R_A.2, U1.7 (DIS)
GND: BZ1.2 (-), C1.2, C2.2, C_PWR.2, D_PWR.1 (K), J1.A1 (GND), J1.A12 (GND), J1.B1 (GND), J1.B12 (GND), J1.S1 (SHIELD), J2.S, RV1.3, R_CC1.2, R_CC2.2, U1.1 (GND)
NOTE_A: R6.2, SW6.1
NOTE_B: R7.2, SW7.1
NOTE_C: R1.2, SW1.1
NOTE_D: R2.2, SW2.1
NOTE_E: R3.2, SW3.1
NOTE_F: R4.2, SW4.1
NOTE_G: R5.2, SW5.1
PWR_LED: D_PWR.2 (A), R_PWR.2
TRIG_THRES: C1.1, SW1.2, SW2.2, SW3.2, SW4.2, SW5.2, SW6.2, SW7.2, U1.2 (TR), U1.6 (THR)

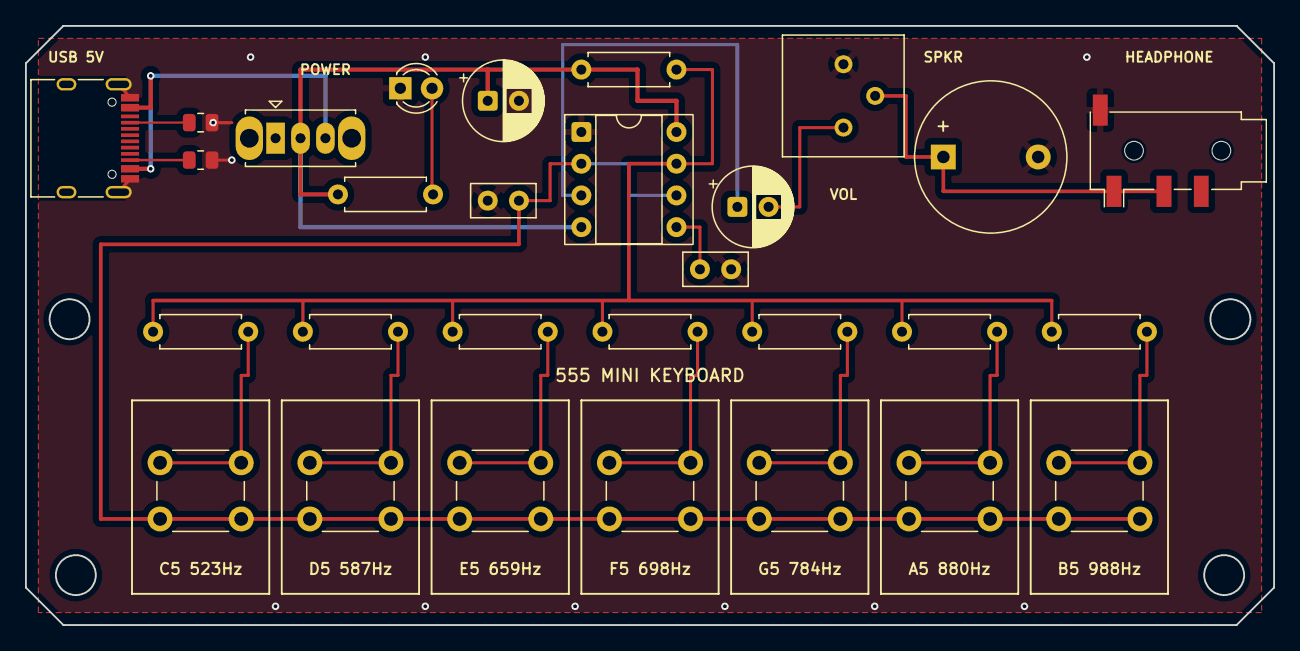
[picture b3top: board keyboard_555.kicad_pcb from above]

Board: 2 copper layers, 100.0 x 48.0 mm, 29 parts (0 on the bottom side), 19 nets.
